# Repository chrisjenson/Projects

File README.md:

# Projects

This is a collection of various labs, projects, and assignments from college and even a couple from before

For more detail about a specific project, look in the that projects folder for the README and or report. Some projects also have a wiki page

Scores, dates, and issues are also included when available

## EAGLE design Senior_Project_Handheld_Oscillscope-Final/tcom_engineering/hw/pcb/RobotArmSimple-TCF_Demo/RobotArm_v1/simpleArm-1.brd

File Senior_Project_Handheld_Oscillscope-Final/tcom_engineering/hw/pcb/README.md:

# pcb

Directory for printed circuit board designs.

One sub-directory for each PCB.

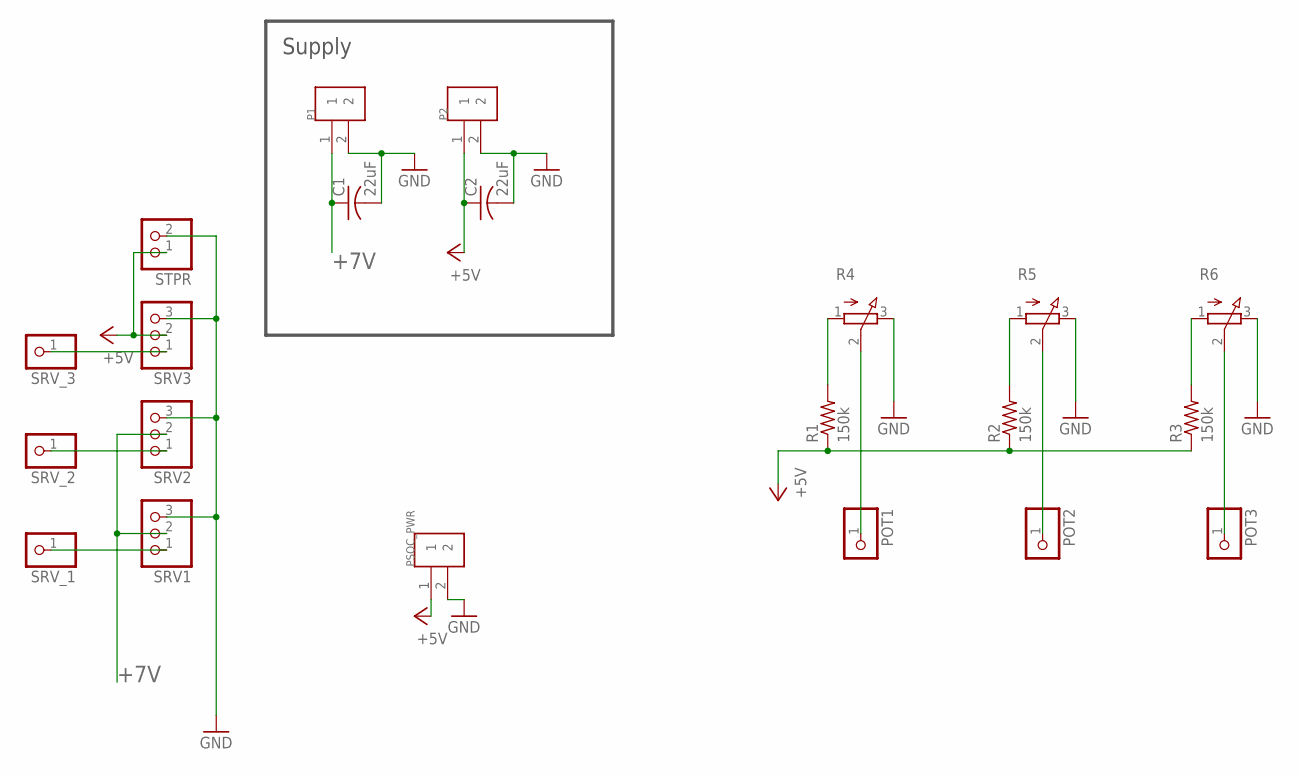
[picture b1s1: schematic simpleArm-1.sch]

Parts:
C1, C2: 22uF; C050-030X075
P1, P2: 282837-2; TE_282837-2
POT1, POT2, POT3: PINHD-1X1; 1X01
PSOC_PWR: 282837-2; TE_282837-2
R1, R2, R3: 150k; 0204/7
R4, R5, R6: 3RP/1610N
SRV1, SRV2, SRV3: PINHD-1X3; 1X03
SRV_1, SRV_2, SRV_3: PINHD-1X1; 1X01
STPR: PINHD-1X2; 1X02

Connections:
+5V: C2.1, P2.1, PSOC_PWR.1, R1.1, R2.1, R3.1, SRV3.2, STPR.1
+7V: C1.1, P1.1, SRV1.2, SRV2.2
GND: C1.2, C2.2, P1.2, P2.2, PSOC_PWR.2, R4.3 (E), R5.3 (E), R6.3 (E), SRV1.3, SRV2.3, SRV3.3, STPR.2
unnamed: R1.2, R4.1 (A)
unnamed: R2.2, R5.1 (A)
unnamed: R3.2, R6.1 (A)
unnamed: POT3.1, R6.2 (S)
unnamed: POT1.1, R4.2 (S)
unnamed: POT2.1, R5.2 (S)
unnamed: SRV3.1, SRV_3.1
unnamed: SRV2.1, SRV_2.1
unnamed: SRV1.1, SRV_1.1

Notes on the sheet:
Supply

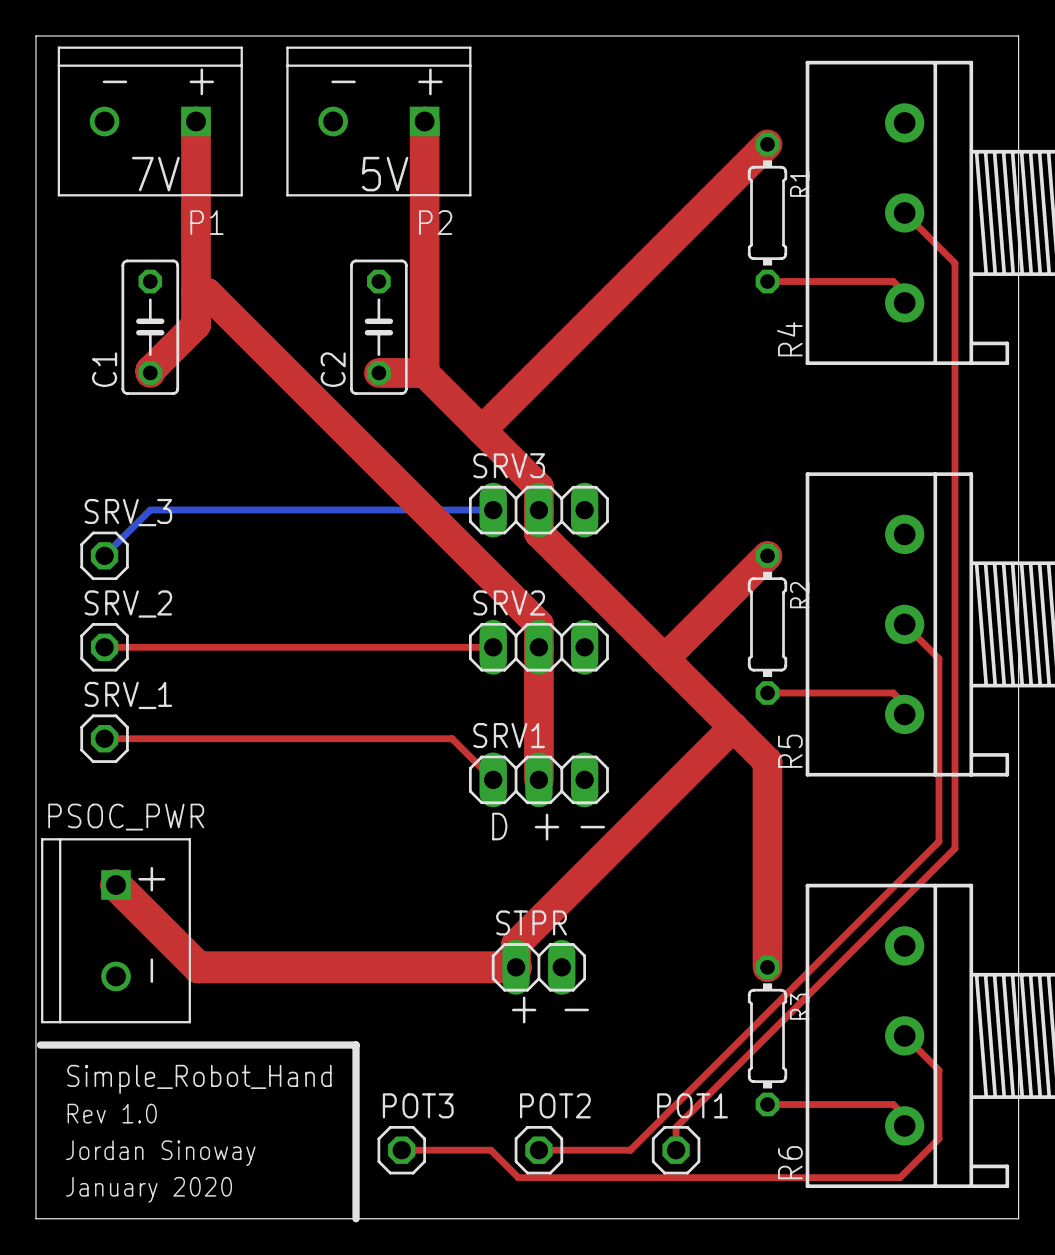
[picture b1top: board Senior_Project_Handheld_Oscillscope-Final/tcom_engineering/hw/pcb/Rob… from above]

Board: 2 copper layers, 54.6 x 65.7 mm, 21 parts (0 on the bottom side), 12 nets.

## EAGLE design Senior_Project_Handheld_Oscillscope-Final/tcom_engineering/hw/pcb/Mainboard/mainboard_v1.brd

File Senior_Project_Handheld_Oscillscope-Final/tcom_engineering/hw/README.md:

# HW - T-COM Hardware

This directory will contain:

* Printed circuit board schematics and design databases
* Electrical bill of materials
* Drawings related to connection and physical configuration of electrical components

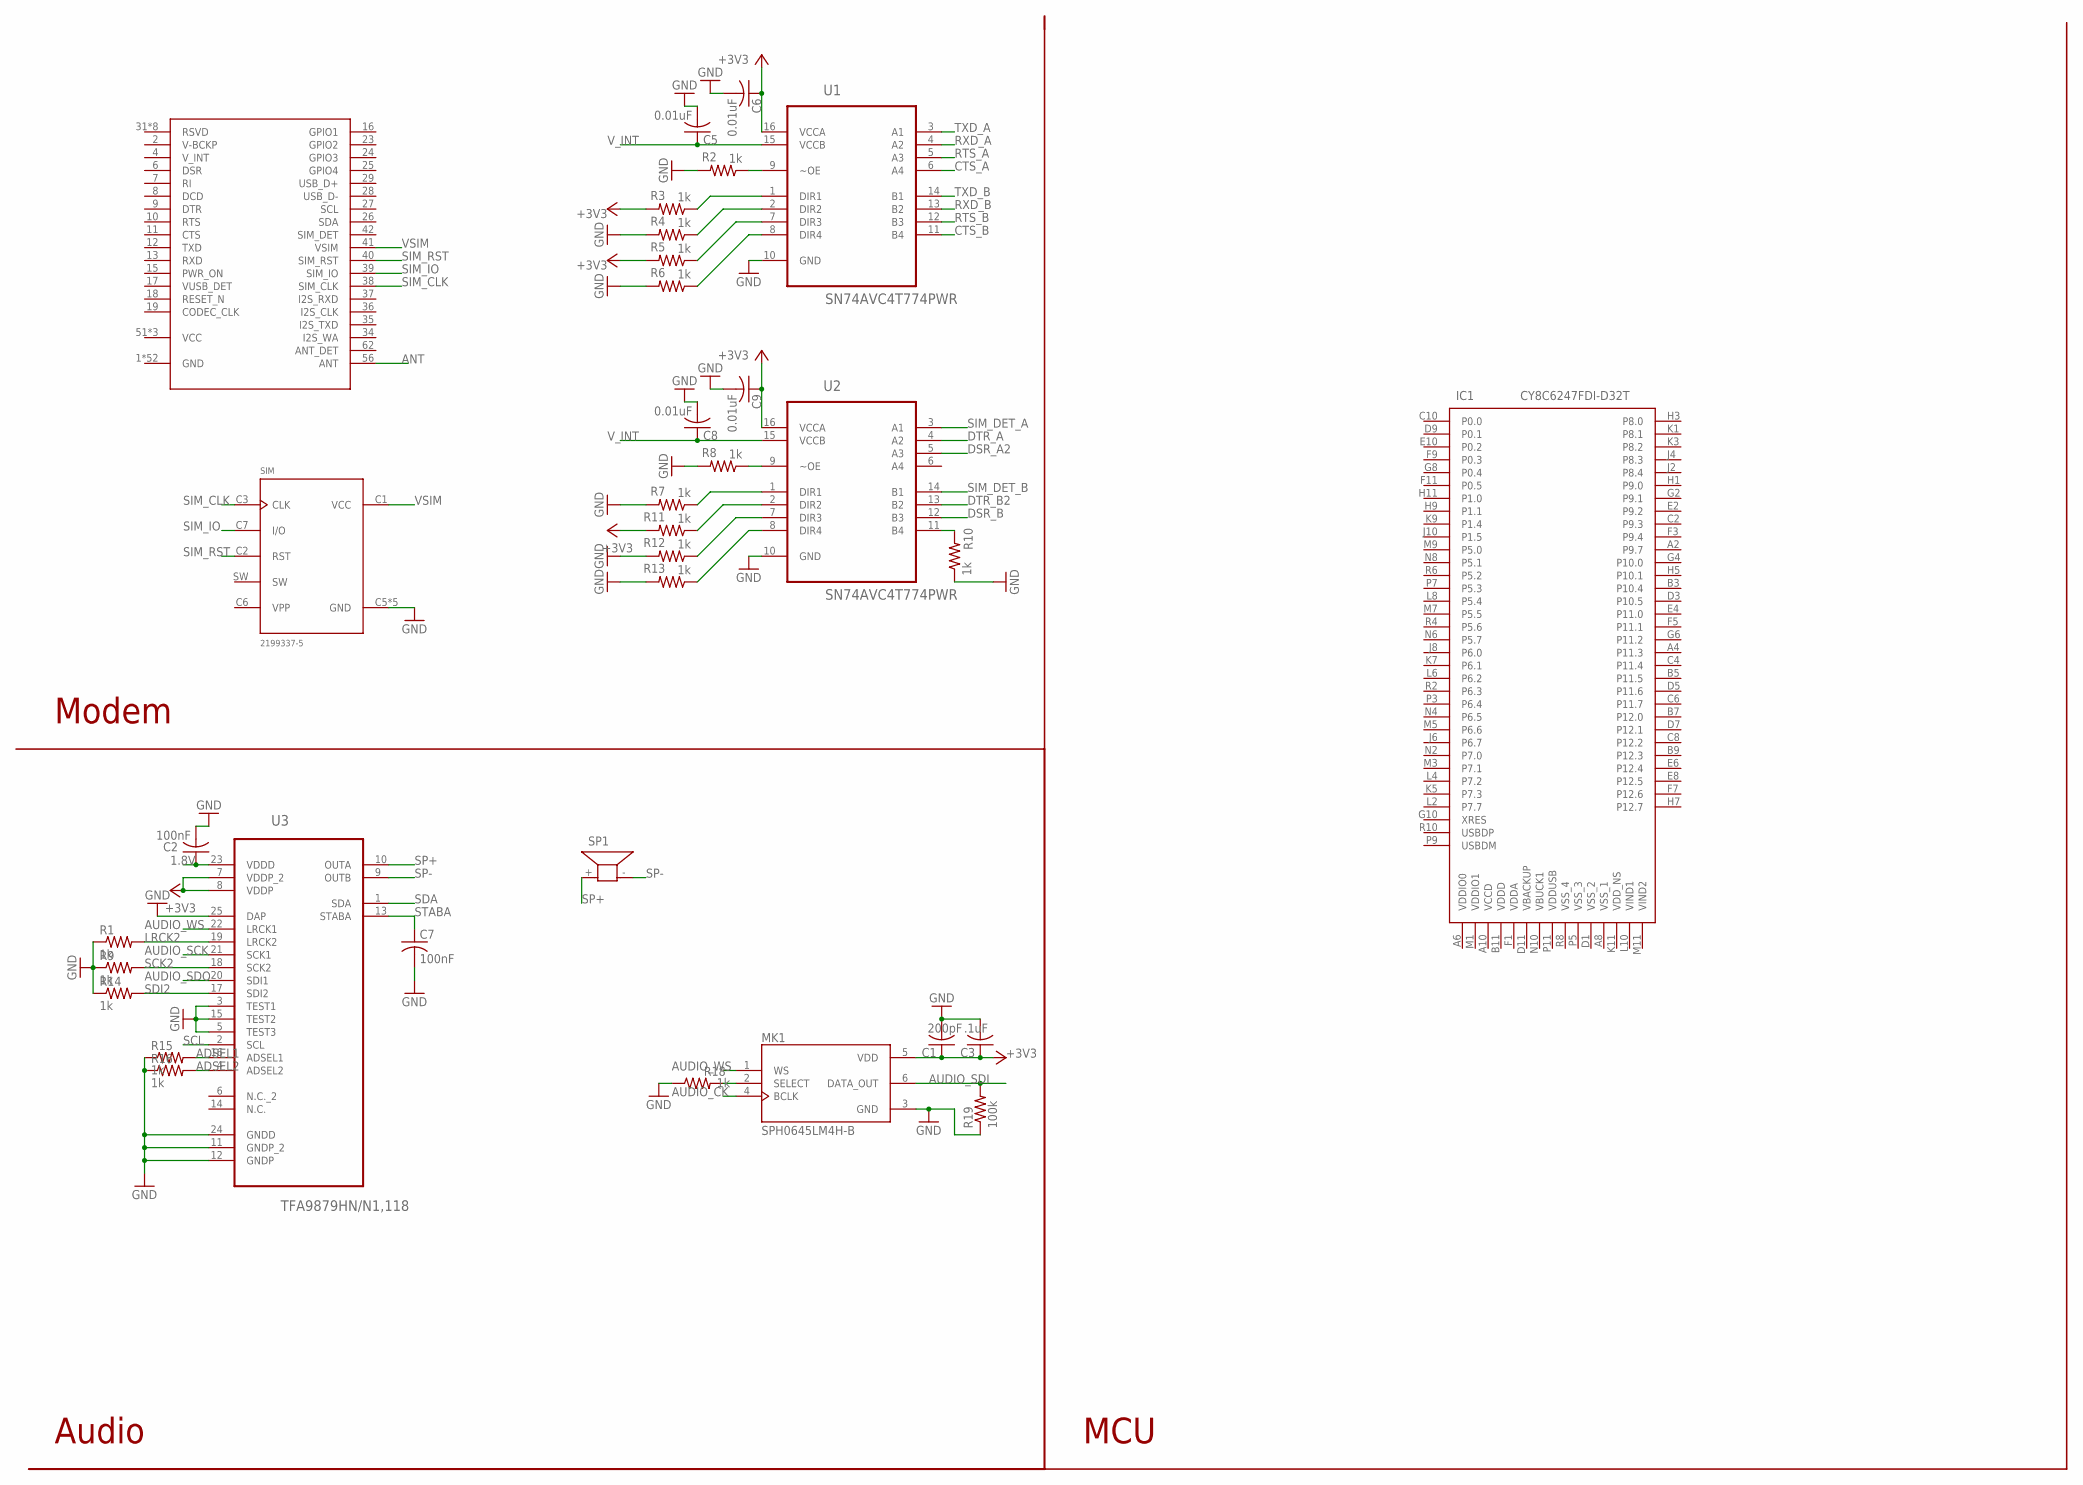
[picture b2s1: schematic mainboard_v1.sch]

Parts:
C1: 200pF; C0603
C2, C7: 100nF; C0603
C3: .1uF; C0603
C5, C6, C8, C9: 0.01uF; C0603
IC1: CY8C6247FDI-D32T; BGA80C30P11X15_368X319X47
MK1: SPH0645LM4H-B; MIC_SPH0645LM4H-B
R1, R2, R3, R4, R5, R6, R7, R8, R9, R10, R11, R12, R13, R14, R15, R16, R18: 1k; R0603
R19: 100k; R0603
SIM: 2199337-5; TE_2199337-5
SP1: KSS1201
U1, U2: SN74AVC4T774PWR; SOP65P640X120-16N
U3: TFA9879HN/N1,118; QFN50P260X260X100-25N
U$1: SARA-U260; XCVR_SARA-N200-02B

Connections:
1.8V: C2.1, U3.23 (VDDD)
+3V3: C1.1, C3.1, C6.1, C9.1, MK1.5 (VDD), R3.2, R5.2, R11.2, U1.16 (VCCA), U2.16 (VCCA), U3.7 (VDDP_2), U3.8 (VDDP)
ADSEL1: R15.2, U3.16 (ADSEL1)
ADSEL2: R16.2, U3.4 (ADSEL2)
ANT: U$1.56 (ANT)
AUDIO_CK: MK1.4 (BCLK)
AUDIO_SCK: U3.21 (SCK1)
AUDIO_SDI: MK1.6 (DATA_OUT), R19.2
AUDIO_SDO: U3.20 (SDI1)
AUDIO_WS: MK1.1 (WS), U3.22 (LRCK1)
CTS_A: U1.6 (A4)
CTS_B: U1.11 (B4)
DSR_A2: U2.5 (A3)
DSR_B: U2.12 (B3)
DTR_A: U2.4 (A2)
DTR_B2: U2.13 (B2)
GND: C1.2, C2.2, C3.2, C5.2, C6.2, C7.2, C8.2, C9.2, MK1.3 (GND), R1.1, R2.2, R4.2, R6.2, R7.2, R8.2, R9.1, R10.1, R12.2, R13.2, R14.1, R15.1, R16.1, R18.1, R19.1, SIM.C5 (GND), SIM.G1 (GND), SIM.G2 (GND), SIM.G3 (GND), SIM.G4 (GND), U1.10 (GND), U2.10 (GND), U3.3 (TEST1), U3.5 (TEST3), U3.11 (GNDP_2), U3.12 (GNDP), U3.15 (TEST2), U3.24 (GNDD), U3.25 (DAP)
LRCK2: R1.2, U3.19 (LRCK2)
unnamed: R3.1, U1.1 (DIR1)
unnamed: R4.1, U1.2 (DIR2)
unnamed: R5.1, U1.7 (DIR3)
unnamed: MK1.2 (SELECT), R18.2
unnamed: R6.1, U1.8 (DIR4)
unnamed: R7.1, U2.1 (DIR1)
unnamed: R11.1, U2.2 (DIR2)
unnamed: R12.1, U2.7 (DIR3)
unnamed: R8.1, U2.9 (~OE)
unnamed: R13.1, U2.8 (DIR4)
unnamed: R10.2, U2.11 (B4)
unnamed: R2.1, U1.9 (~OE)
RTS_A: U1.5 (A3)
RTS_B: U1.12 (B3)
RXD_A: U1.4 (A2)
RXD_B: U1.13 (B2)
SCK2: R9.2, U3.18 (SCK2)
SCL: U3.2 (SCL)
SDA: U3.1 (SDA)
SDI2: R14.2, U3.17 (SDI2)
SIM_CLK: SIM.C3 (CLK), U$1.38 (SIM_CLK)
SIM_DET_A: U2.3 (A1)
SIM_DET_B: U2.14 (B1)
SIM_IO: SIM.C7 (I/O), U$1.39 (SIM_IO)
SIM_RST: SIM.C2 (RST), U$1.40 (SIM_RST)
SP+: SP1.+ (1), U3.10 (OUTA)
SP-: SP1.- (2), U3.9 (OUTB)
STABA: C7.1, U3.13 (STABA)
TXD_A: U1.3 (A1)
TXD_B: U1.14 (B1)
VSIM: SIM.C1 (VCC), U$1.41 (VSIM)
V_INT: C5.1, C8.1, U1.15 (VCCB), U2.15 (VCCB)

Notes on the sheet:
Modem
Audio
MCU

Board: 4 copper layers, 34 parts (0 on the bottom side), 30 nets, no tracks yet.

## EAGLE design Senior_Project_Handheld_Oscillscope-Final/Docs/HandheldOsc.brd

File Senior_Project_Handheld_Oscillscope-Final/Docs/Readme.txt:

Folder for proposals, preliminary documents, and other documentation

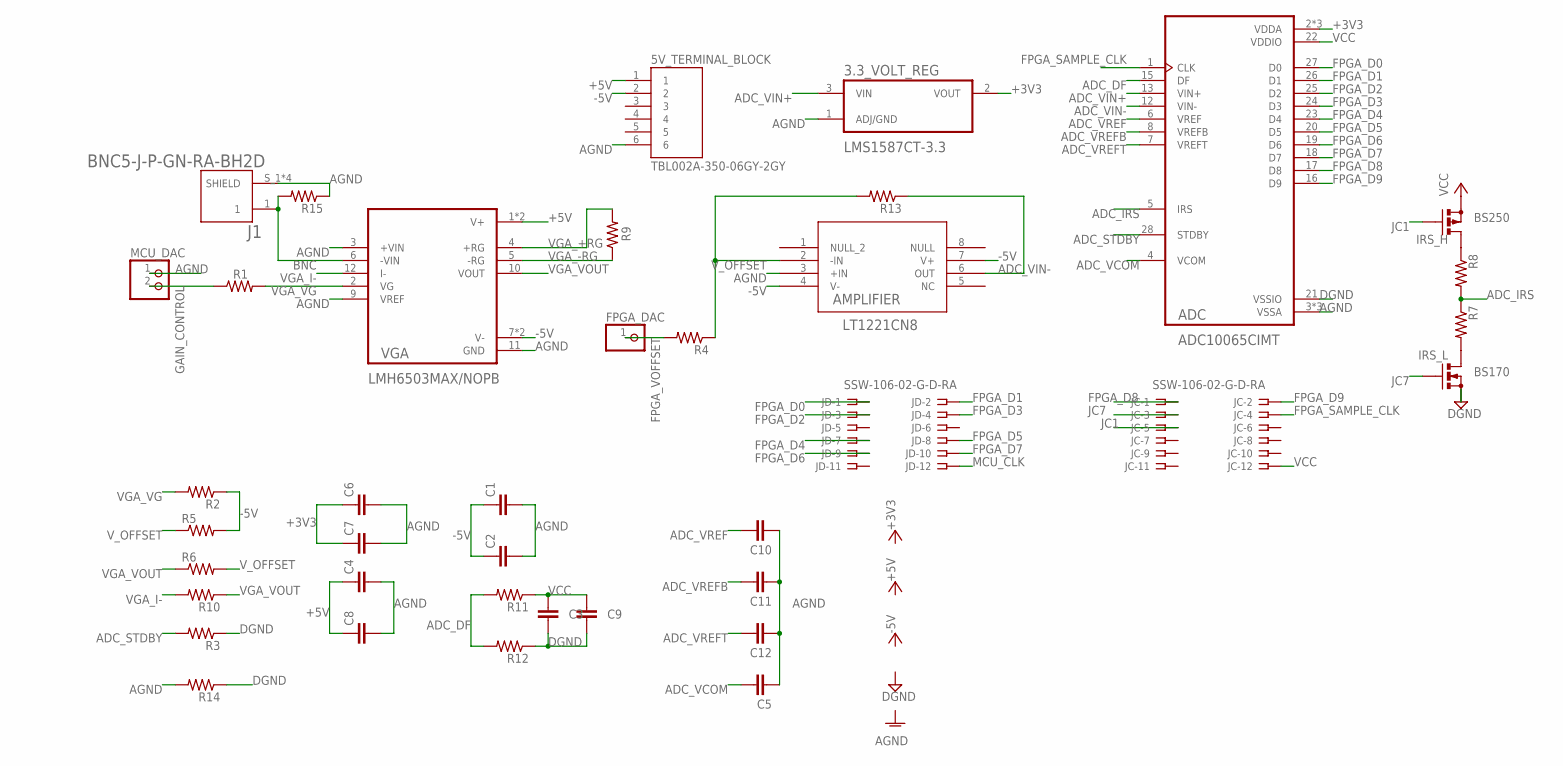
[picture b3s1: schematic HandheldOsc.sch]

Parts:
3.3_VOLT_REG: LMS1587CT-3.3; TO254P1054X470X1955-3
5V_TERMINAL_BLOCK: TBL002A-350-06GY-2GY; CUI_TBL002A-350-06GY-2GY
ADC: ADC10065CIMT; SOP65P640X120-28N
AMPLIFIER: LT1221CN8; PDIP-8_N
C1, C2, C3, C4, C5, C6, C7, C8, C9, C10, C11, C12: C2,5-3; C2.5-3
FPGA_DAC: PINHD-1X1; 1X01
IRS_H: BS250; SOT54E
IRS_L: BS170; SOT54E
J1: BNC5-J-P-GN-RA-BH2D; SAMTEC_BNC5-J-P-GN-RA-BH2D
JC: SSW-106-02-G-D-RA
JD: SSW-106-02-G-D-RA
MCU_DAC: PINHD-1X2; 1X02
R1, R2, R3, R4, R5, R6, R7, R8, R9, R10, R11, R12, R13, R14, R15: R-US_0207/12; 0207/12
VGA: LMH6503MAX/NOPB; SOIC127P600X175-14N

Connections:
+3V3: 3.3_VOLT_REG.2 (VOUT), ADC.2 (VDDA), ADC.9 (VDDA), ADC.10 (VDDA), C6.1, C7.1
+5V: 5V_TERMINAL_BLOCK.1, C4.1, C8.1, VGA.1 (V+), VGA.14 (V+)
-5V: 5V_TERMINAL_BLOCK.2, AMPLIFIER.4 (V-), AMPLIFIER.7 (V+), C1.1, C2.1, R2.1, R5.2, VGA.7 (V-), VGA.8 (V-)
ADC_DF: ADC.15 (DF), R11.2, R12.2
ADC_IRS: ADC.5 (IRS), R7.1, R8.2
ADC_STDBY: ADC.28 (STDBY), R3.2
ADC_VCOM: ADC.4 (VCOM), C5.1
ADC_VIN+: 3.3_VOLT_REG.3 (VIN), ADC.13 (VIN+)
ADC_VIN-: ADC.12 (VIN-), AMPLIFIER.6 (OUT), R13.1
ADC_VREF: ADC.6 (VREF), C10.1
ADC_VREFB: ADC.8 (VREFB), C11.1
ADC_VREFT: ADC.7 (VREFT), C12.1
AGND: 3.3_VOLT_REG.1 (ADJ/GND), 5V_TERMINAL_BLOCK.6, ADC.3 (VSSA), ADC.11 (VSSA), ADC.14 (VSSA), AMPLIFIER.3 (+IN), C1.2, C2.2, C4.2, C5.2, C6.2, C7.2, C8.2, C10.2, C11.2, C12.2, J1.S_1 (SHIELD), J1.S_2 (SHIELD), J1.S_3 (SHIELD), J1.S_4 (SHIELD), MCU_DAC.1, R14.2, R15.1, VGA.3 (+VIN), VGA.9 (VREF), VGA.11 (GND)
BNC: J1.1, R15.2, VGA.6 (-VIN)
DGND: ADC.21 (VSSIO), C3.2, C9.2, IRS_L.S, R3.1, R12.1, R14.1
FPGA_D0: ADC.27 (D0), JD.1
FPGA_D1: ADC.26 (D1), JD.2
FPGA_D2: ADC.25 (D2), JD.3
FPGA_D3: ADC.24 (D3), JD.4
FPGA_D4: ADC.23 (D4), JD.7
FPGA_D5: ADC.20 (D5), JD.8
FPGA_D6: ADC.19 (D6), JD.9
FPGA_D7: ADC.18 (D7), JD.10
FPGA_D8: ADC.17 (D8), JC.1
FPGA_D9: ADC.16 (D9), JC.2
FPGA_SAMPLE_CLK: ADC.1 (CLK), JC.4
FPGA_VOFFSET: FPGA_DAC.1, R4.2
GAIN_CONTROL: MCU_DAC.2, R1.1
JC1: IRS_H.G, JC.5
JC7: IRS_L.G, JC.3
MCU_CLK: JD.12
unnamed: IRS_H.D, R8.1
unnamed: IRS_L.D, R7.2
VCC: ADC.22 (VDDIO), C3.1, C9.1, IRS_H.S, JC.12, R11.1
VGA_+RG: R9.2, VGA.4 (+RG)
VGA_-RG: R9.1, VGA.5 (-RG)
VGA_I-: R10.2, VGA.12 (I-)
VGA_VG: R1.2, R2.2, VGA.2 (VG)
VGA_VOUT: R6.1, R10.1, VGA.10 (VOUT)
V_OFFSET: AMPLIFIER.2 (-IN), R4.1, R5.1, R6.2, R13.2

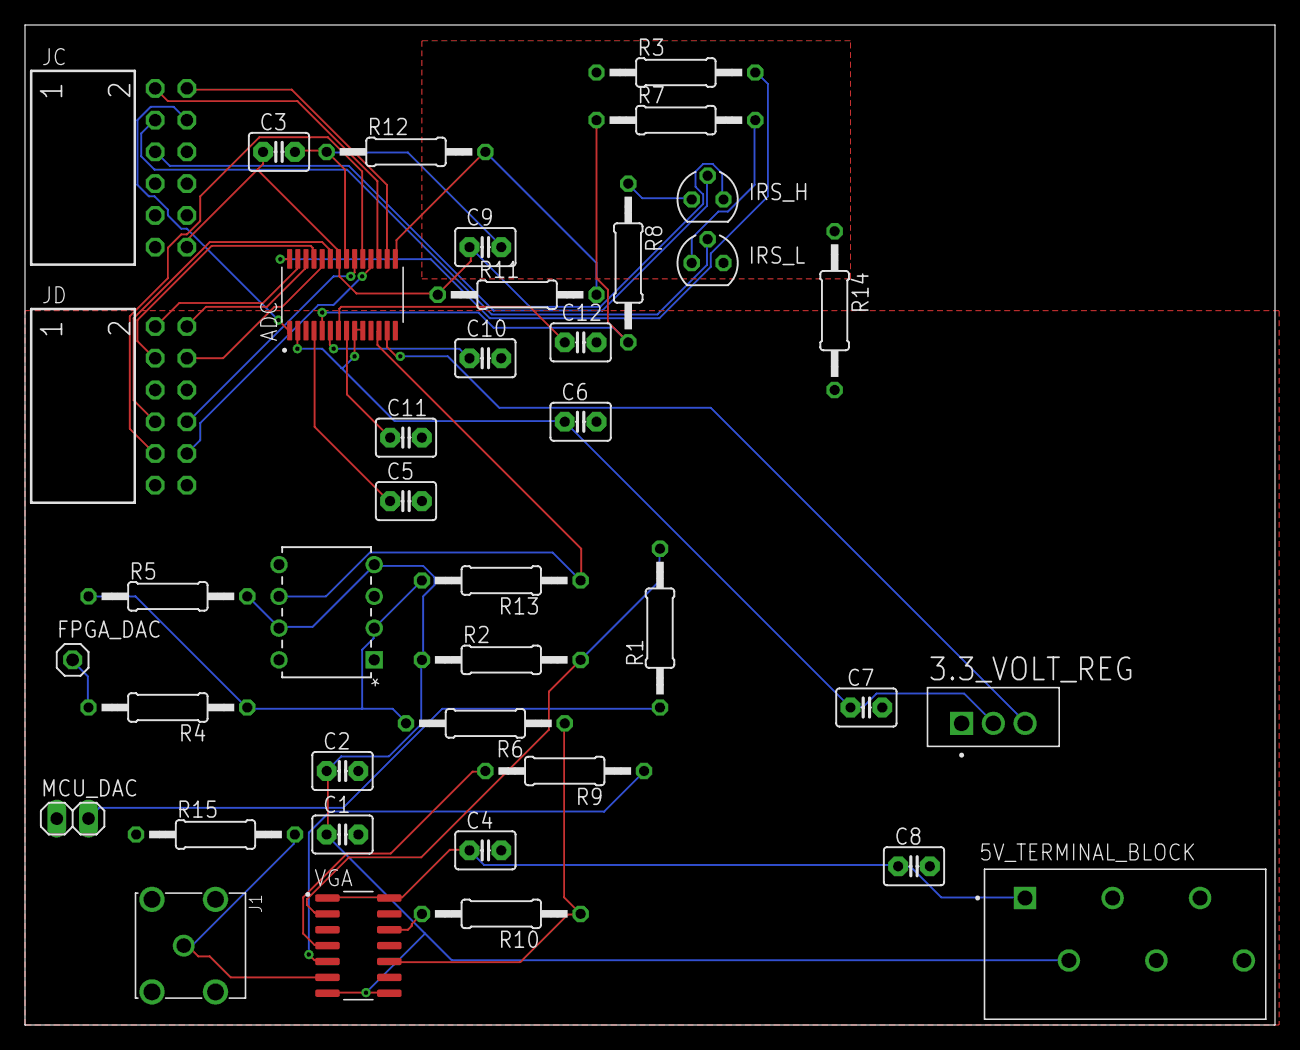
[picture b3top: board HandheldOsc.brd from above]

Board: 2 copper layers, 100.0 x 80.0 mm, 39 parts (0 on the bottom side), 39 nets.

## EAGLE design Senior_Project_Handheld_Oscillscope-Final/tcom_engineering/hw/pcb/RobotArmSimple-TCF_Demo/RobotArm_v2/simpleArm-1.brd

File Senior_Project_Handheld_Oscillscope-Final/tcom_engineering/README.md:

# T-COM Engineering

Repository for T-COM design files and documentation

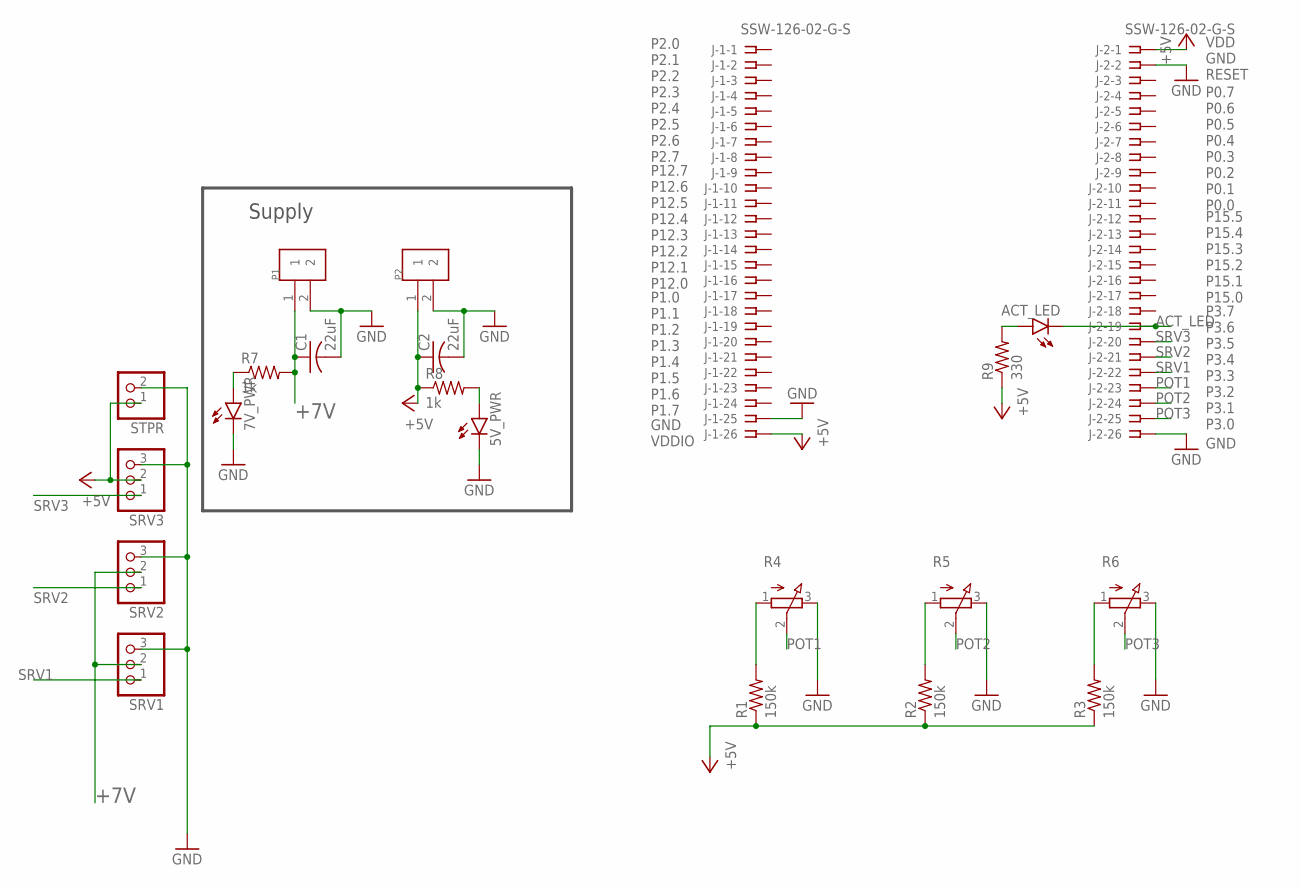
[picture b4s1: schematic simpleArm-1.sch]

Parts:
5V_PWR, 7V_PWR: LED3MM
ACT_LED: LED3MM
C1, C2: 22uF; C050-030X075
J-1, J-2: SSW-126-02-G-S
P1, P2: 282837-2; TE_282837-2
R1, R2, R3: 150k; 0204/7
R4, R5, R6: 3RP/1610N
R7, R8: 1k; 0204/7
R9: 330; 0204/7
SRV1, SRV2, SRV3: PINHD-1X3; 1X03
STPR: PINHD-1X2; 1X02

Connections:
+5V: C2.1, J-1.26, J-2.1, P2.1, R1.1, R2.1, R3.1, R8.1, R9.1, SRV3.2, STPR.1
+7V: C1.1, P1.1, R7.2, SRV1.2, SRV2.2
ACT_LED: ACT_LED.K (C), J-2.19
GND: 5V_PWR.K (C), 7V_PWR.K (C), C1.2, C2.2, J-1.25, J-2.2, J-2.26, P1.2, P2.2, R4.3 (E), R5.3 (E), R6.3 (E), SRV1.3, SRV2.3, SRV3.3, STPR.2
unnamed: R1.2, R4.1 (A)
unnamed: R2.2, R5.1 (A)
unnamed: R3.2, R6.1 (A)
unnamed: 7V_PWR.A, R7.1
unnamed: 5V_PWR.A, R8.2
unnamed: ACT_LED.A, R9.2
POT1: J-2.23, R4.2 (S)
POT2: J-2.24, R5.2 (S)
POT3: J-2.25, R6.2 (S)
SRV1: J-2.22, SRV1.1
SRV2: J-2.21, SRV2.1
SRV3: J-2.20, SRV3.1

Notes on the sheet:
Supply
P2.0 P2.1 P2.2 P2.3 P2.4 P2.5 P2.6 P2.7
P12.7 P12.6 P12.5 P12.4 P12.3 P12.2 P12.1 P12.0
P1.0 P1.1 P1.2 P1.3 P1.4 P1.5 P1.6 P1.7
GND VDDIO
GND
P3.7 P3.6 P3.5 P3.4 P3.3 P3.2 P3.1 P3.0
P15.5 P15.4 P15.3 P15.2 P15.1 P15.0
P0.7 P0.6 P0.5 P0.4 P0.3 P0.2 P0.1 P0.0
VDD GND RESET

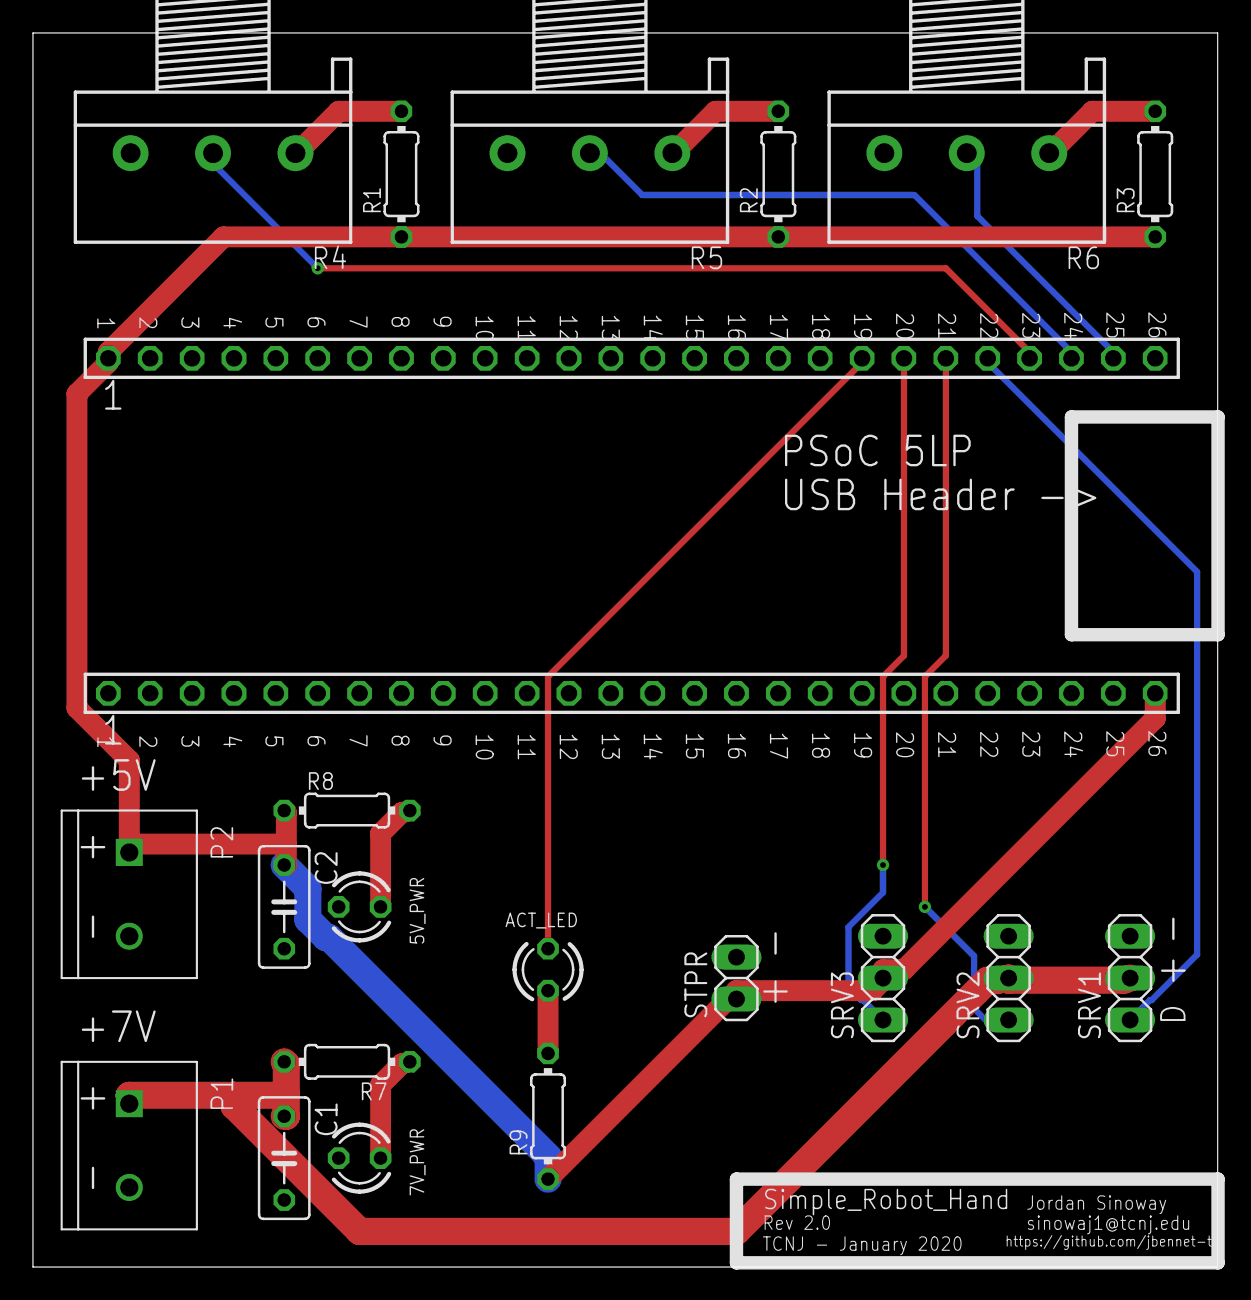
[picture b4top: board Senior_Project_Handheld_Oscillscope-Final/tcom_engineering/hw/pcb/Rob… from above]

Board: 2 copper layers, 71.9 x 74.9 mm, 22 parts (0 on the bottom side), 16 nets.

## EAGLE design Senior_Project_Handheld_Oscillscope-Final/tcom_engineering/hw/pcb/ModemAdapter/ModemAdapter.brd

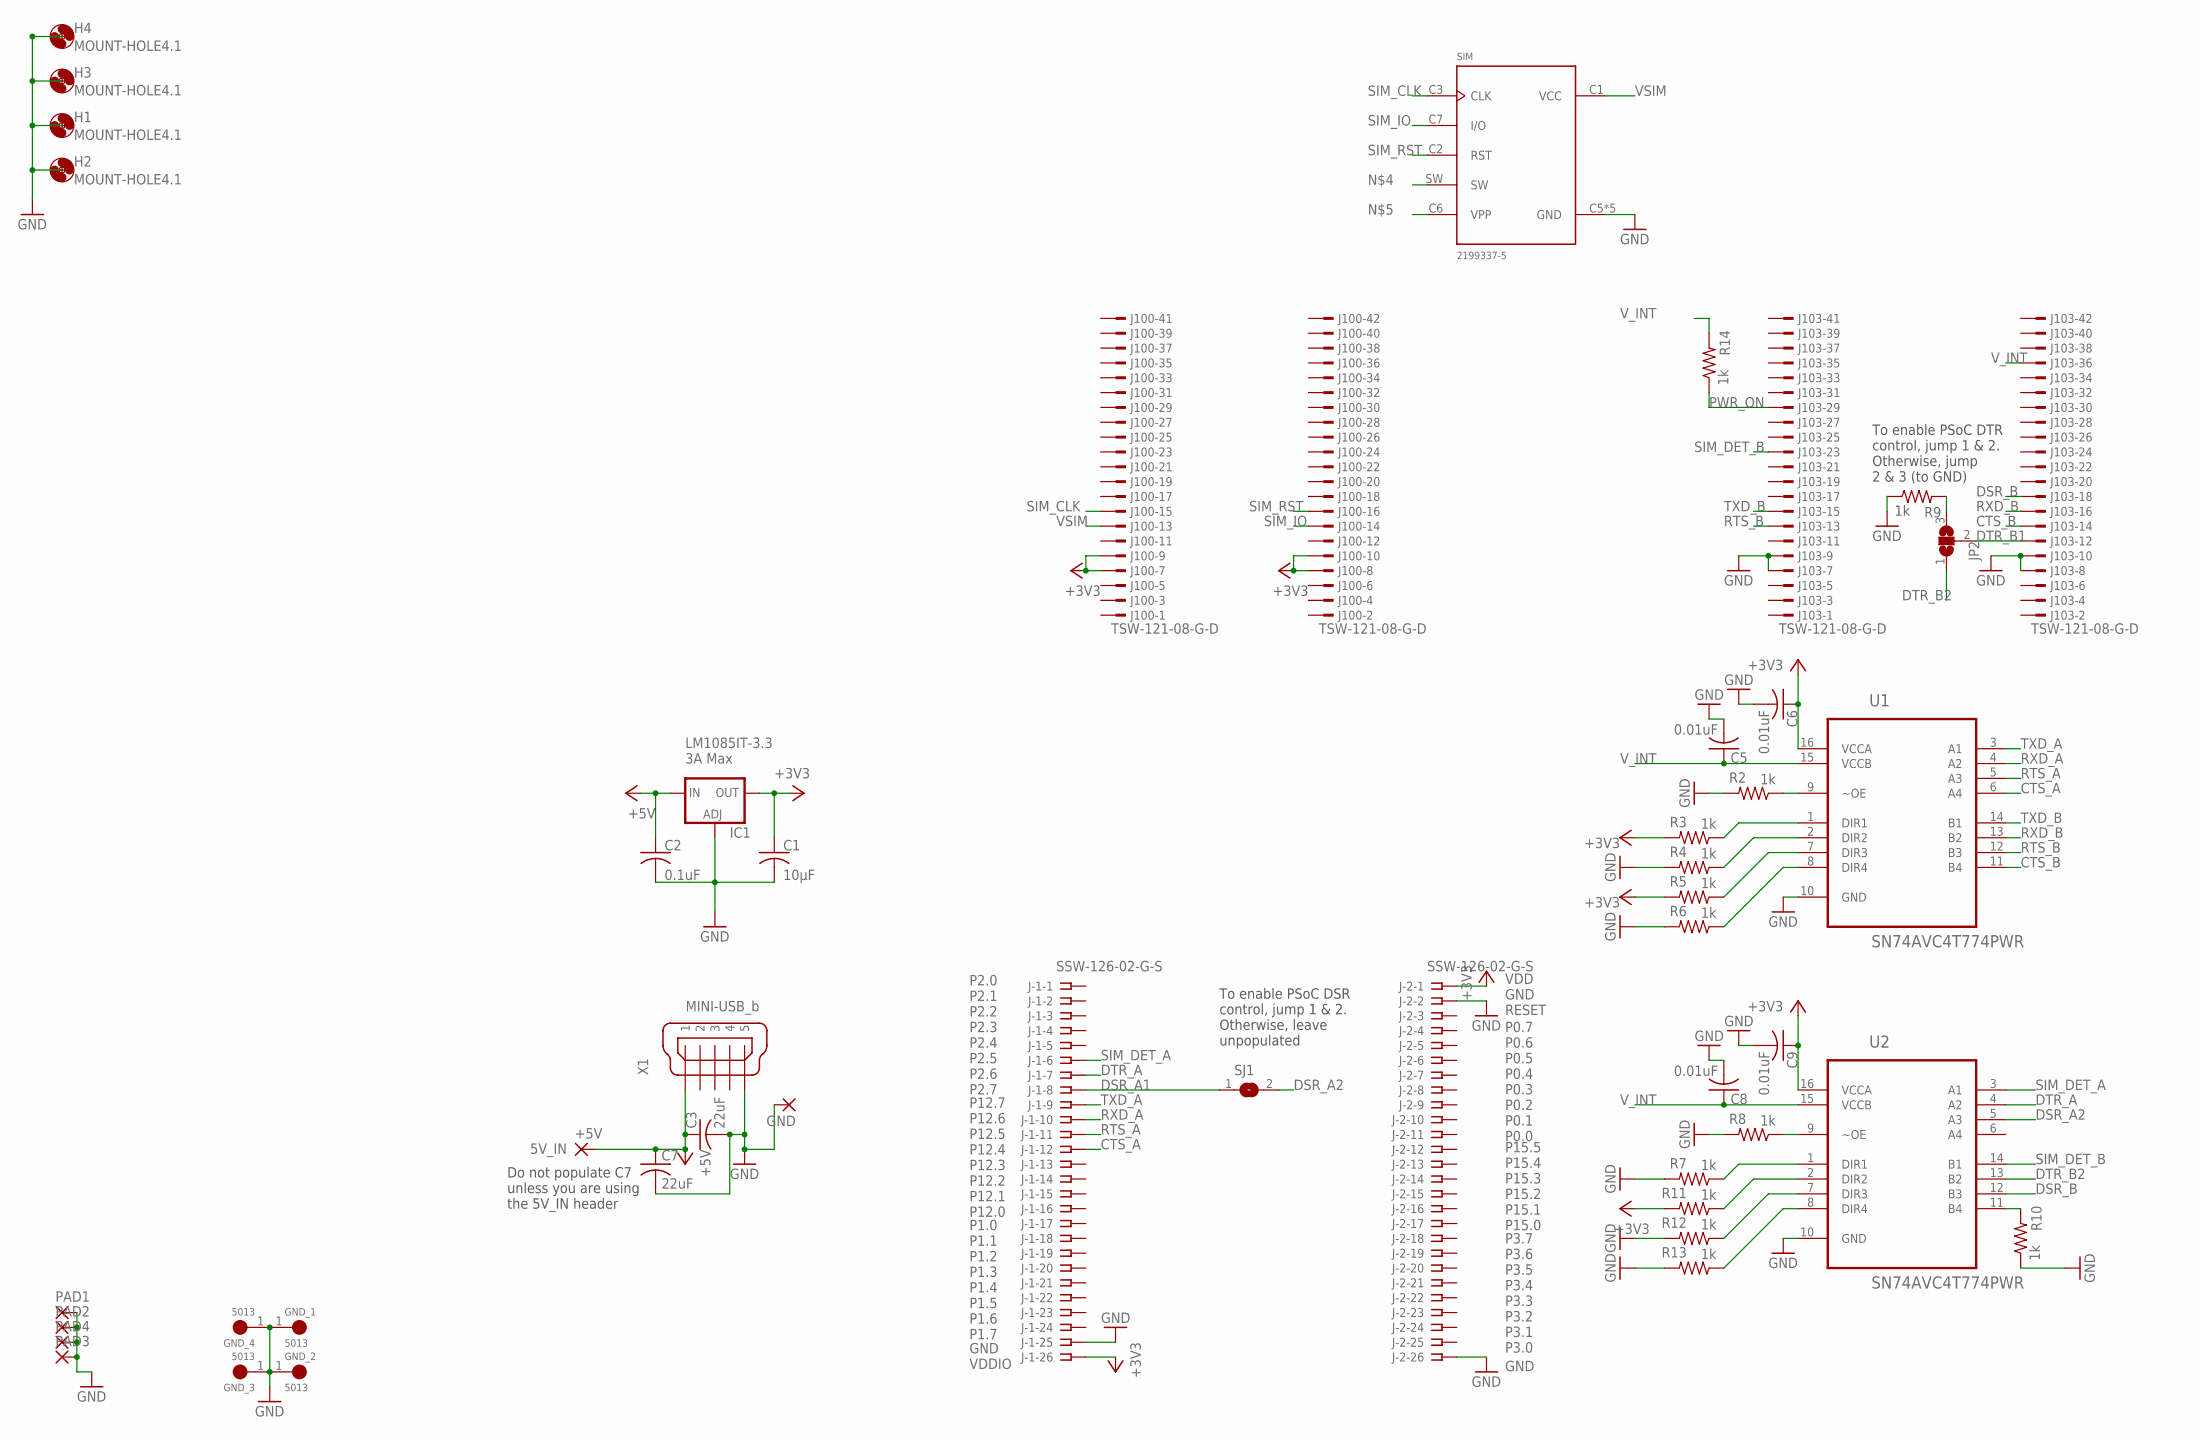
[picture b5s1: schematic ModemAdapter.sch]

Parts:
+5V: 5V_IN; 3,17/1,1
C1: 10μF; C050-024X044
C2: 0.1uF; C050-024X044
C3, C7: 22uF; C050-024X044
C5, C6, C8, C9: 0.01uF; C050-024X044
GND: 3,17/1,1
GND_1, GND_2, GND_3, GND_4: 5013; TESTPOINT_5013
H1, H2, H3, H4: MOUNT-HOLE4.1; 4,1
IC1: LD117AV33; TO220L1
J100, J103: TSW-121-08-G-D; TSW-121-XX-G-D
J-1, J-2: SSW-126-02-G-S
JP2: SJ2W; SJ_2
PAD1, PAD2, PAD3, PAD4: SMD2; SMD1,27-2,54
R2, R3, R4, R5, R6, R7, R8, R9, R10, R11, R12, R13, R14: 1k; 0204/7
SIM: 2199337-5; TE_2199337-5
SJ1: SJ
U1, U2: SN74AVC4T774PWR; SOP65P640X120-16N
X1: MINI-USB_b; 32005-601

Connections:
+3V3: C1.1, C6.1, C9.1, IC1.2 (OUT), J100.7, J100.8, J100.9, J100.10, J-1.26, J-2.1, R3.2, R5.2, R11.2, U1.16 (VCCA), U2.16 (VCCA)
+5V: +5V.1, C2.1, C3.1, C7.1, IC1.3 (IN), X1.1
CTS_A: J-1.12, U1.6 (A4)
CTS_B: J103.14, U1.11 (B4)
DSR_A1: J-1.8, SJ1.1
DSR_A2: SJ1.2, U2.5 (A3)
DSR_B: J103.18, U2.12 (B3)
DTR_A: J-1.7, U2.4 (A2)
DTR_B1: J103.12, JP2.2
DTR_B2: JP2.1, U2.13 (B2)
GND: C1.2, C2.2, C3.2, C5.2, C6.2, C7.2, C8.2, C9.2, GND.1, GND_1.1, GND_2.1, GND_3.1, GND_4.1, IC1.1 (ADJ), J103.7, J103.8, J103.9, J103.10, J-1.25, J-2.2, J-2.26, PAD1.1, PAD2.1, PAD3.1, PAD4.1, R2.2, R4.2, R6.2, R7.2, R8.2, R9.1, R10.1, R12.2, R13.2, SIM.C5 (GND), SIM.G1 (GND), SIM.G2 (GND), SIM.G3 (GND), SIM.G4 (GND), U1.10 (GND), U2.10 (GND), X1.5
unnamed: R3.1, U1.1 (DIR1)
unnamed: R4.1, U1.2 (DIR2)
unnamed: R5.1, U1.7 (DIR3)
unnamed: R6.1, U1.8 (DIR4)
unnamed: R7.1, U2.1 (DIR1)
unnamed: R11.1, U2.2 (DIR2)
unnamed: R12.1, U2.7 (DIR3)
unnamed: R8.1, U2.9 (~OE)
unnamed: JP2.3, R9.2
unnamed: R13.1, U2.8 (DIR4)
unnamed: R10.2, U2.11 (B4)
unnamed: R2.1, U1.9 (~OE)
PWR_ON: J103.29, R14.1
RTS_A: J-1.11, U1.5 (A3)
RTS_B: J103.13, U1.12 (B3)
RXD_A: J-1.10, U1.4 (A2)
RXD_B: J103.16, U1.13 (B2)
SIM_CLK: J100.15, SIM.C3 (CLK)
SIM_DET_A: J-1.6, U2.3 (A1)
SIM_DET_B: J103.23, U2.14 (B1)
SIM_IO: J100.14, SIM.C7 (I/O)
SIM_RST: J100.16, SIM.C2 (RST)
TXD_A: J-1.9, U1.3 (A1)
TXD_B: J103.15, U1.14 (B1)
VSIM: J100.13, SIM.C1 (VCC)
V_INT: C5.1, C8.1, J103.36, R14.2, U1.15 (VCCB), U2.15 (VCCB)

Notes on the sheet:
LM1085IT-3.3 3A Max
Do not populate C7 unless you are using the 5V_IN header
To enable PSoC DTR control, jump 1 & 2. Otherwise, jump 2 & 3 (to GND)
To enable PSoC DSR control, jump 1 & 2. Otherwise, leave unpopulated
P2.0 P2.1 P2.2 P2.3 P2.4 P2.5 P2.6 P2.7
P12.7 P12.6 P12.5 P12.4 P12.3 P12.2 P12.1 P12.0
P1.0 P1.1 P1.2 P1.3 P1.4 P1.5 P1.6 P1.7
GND VDDIO
GND
P3.7 P3.6 P3.5 P3.4 P3.3 P3.2 P3.1 P3.0
P15.5 P15.4 P15.3 P15.2 P15.1 P15.0
P0.7 P0.6 P0.5 P0.4 P0.3 P0.2 P0.1 P0.0
VDD GND RESET

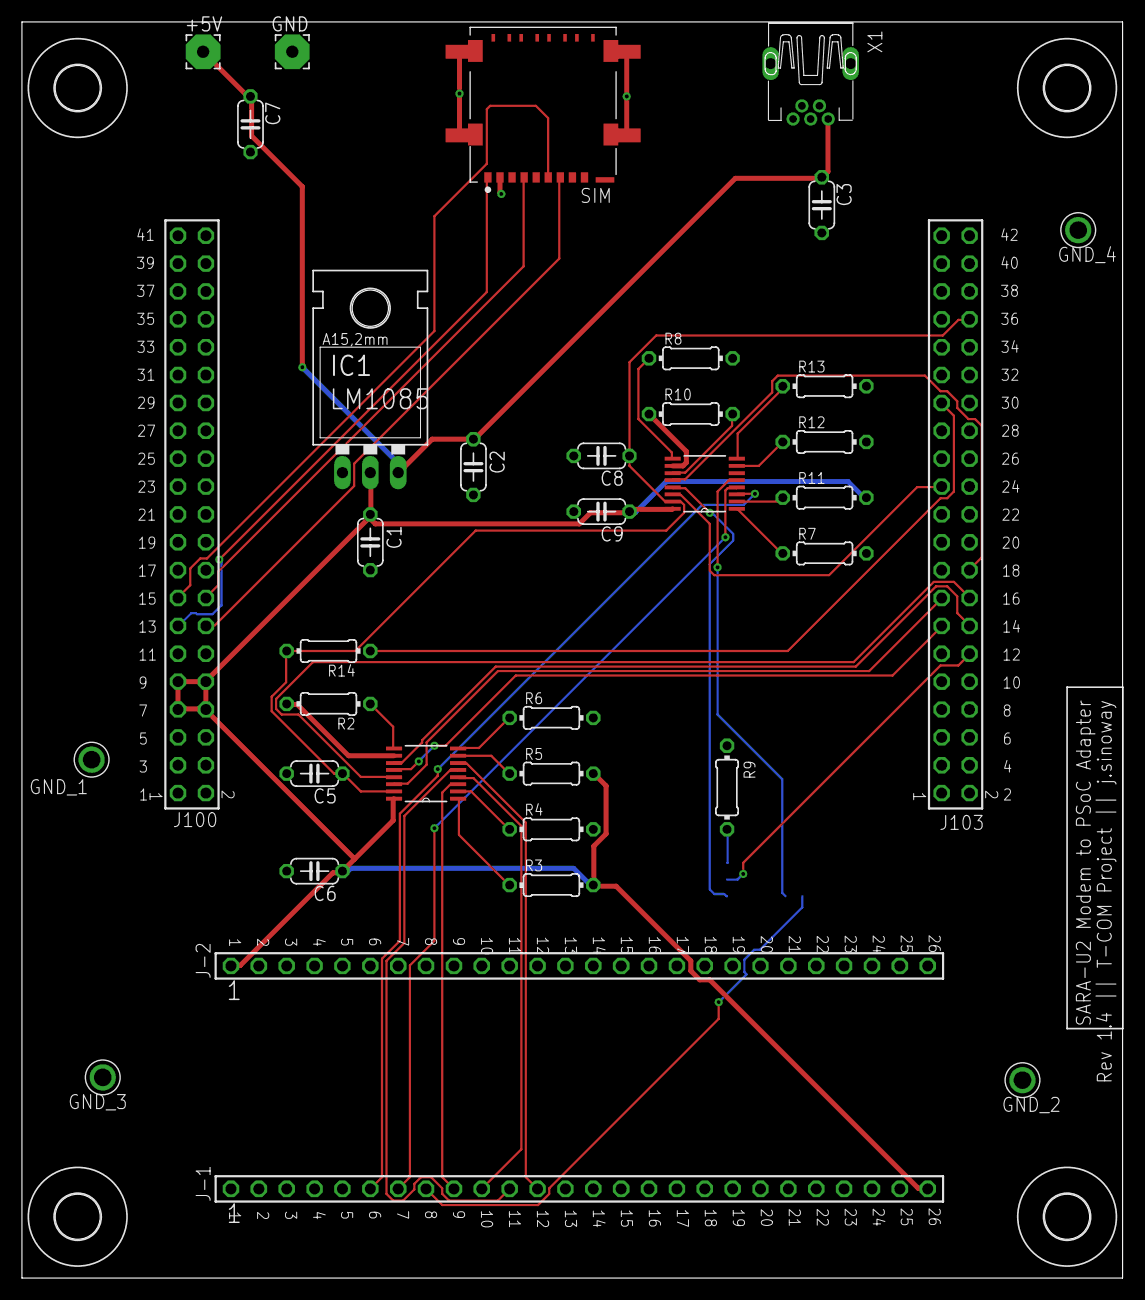
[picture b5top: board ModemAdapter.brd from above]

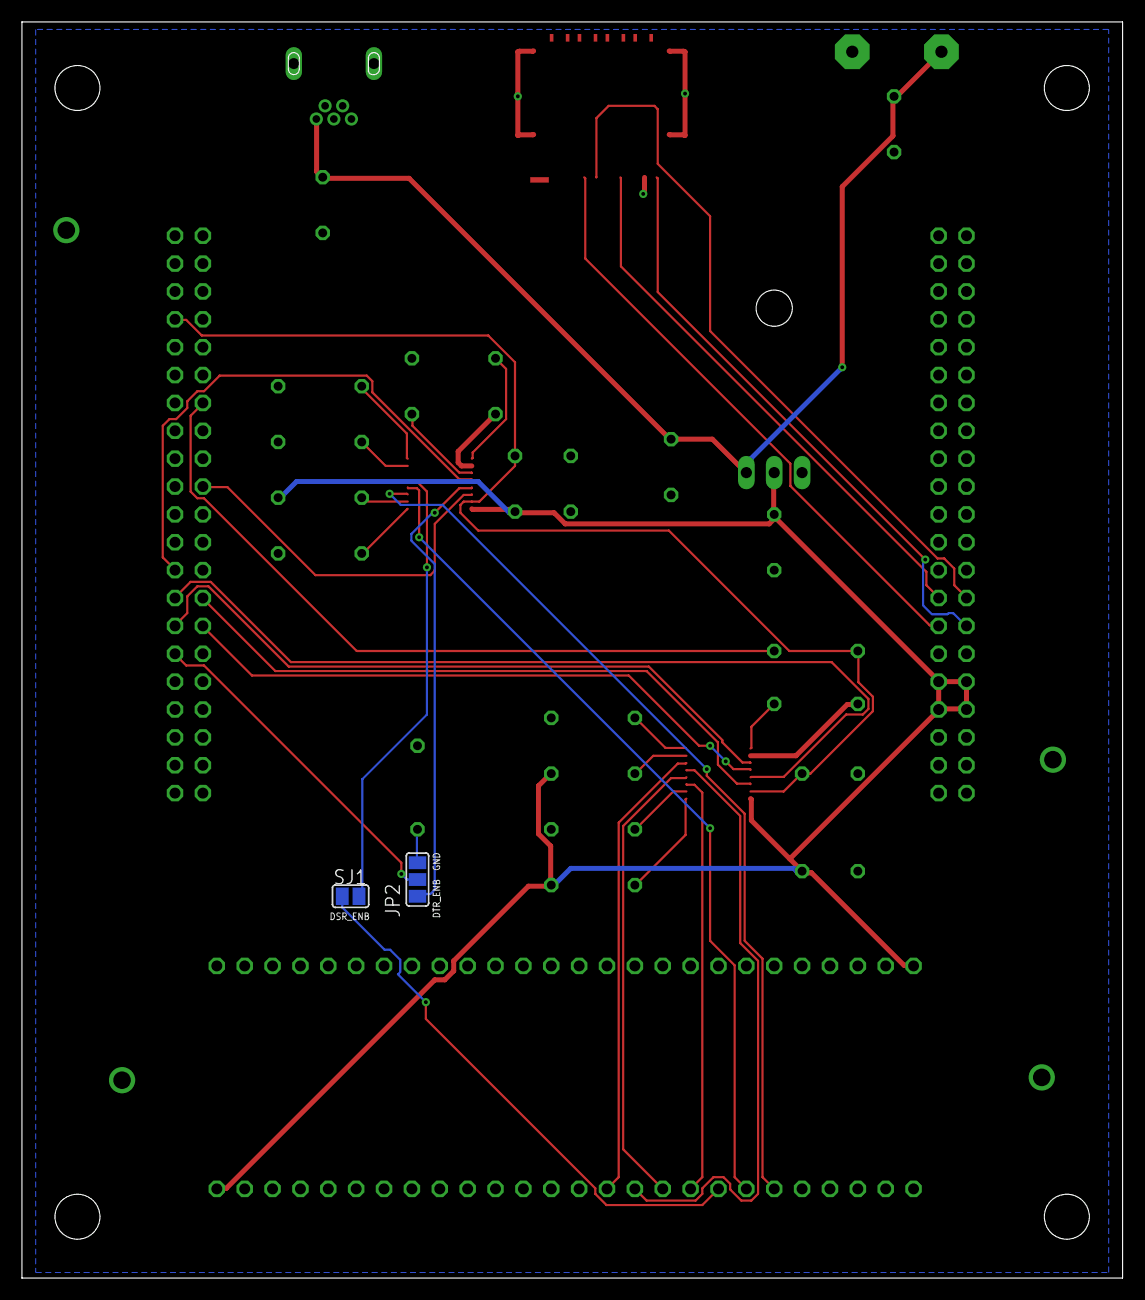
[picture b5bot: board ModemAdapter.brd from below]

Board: 2 copper layers, 100.3 x 114.5 mm, 46 parts (2 on the bottom side), 37 nets.
